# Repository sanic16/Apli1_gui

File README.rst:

============================
IOT Electrónica Aplicada 1
============================

Descripción
===========

Este es un repositorio que contiene el software de comunicación M.Q.T.T. para dispositivos
ESP8266 y ESP32, además de interfaces gráficas para su control.

Autores
========
Julio Sanic, 2022
Alejandro Camey, 2022

Requerimientos
===============

* Python3
* Tkinter
* Micropython

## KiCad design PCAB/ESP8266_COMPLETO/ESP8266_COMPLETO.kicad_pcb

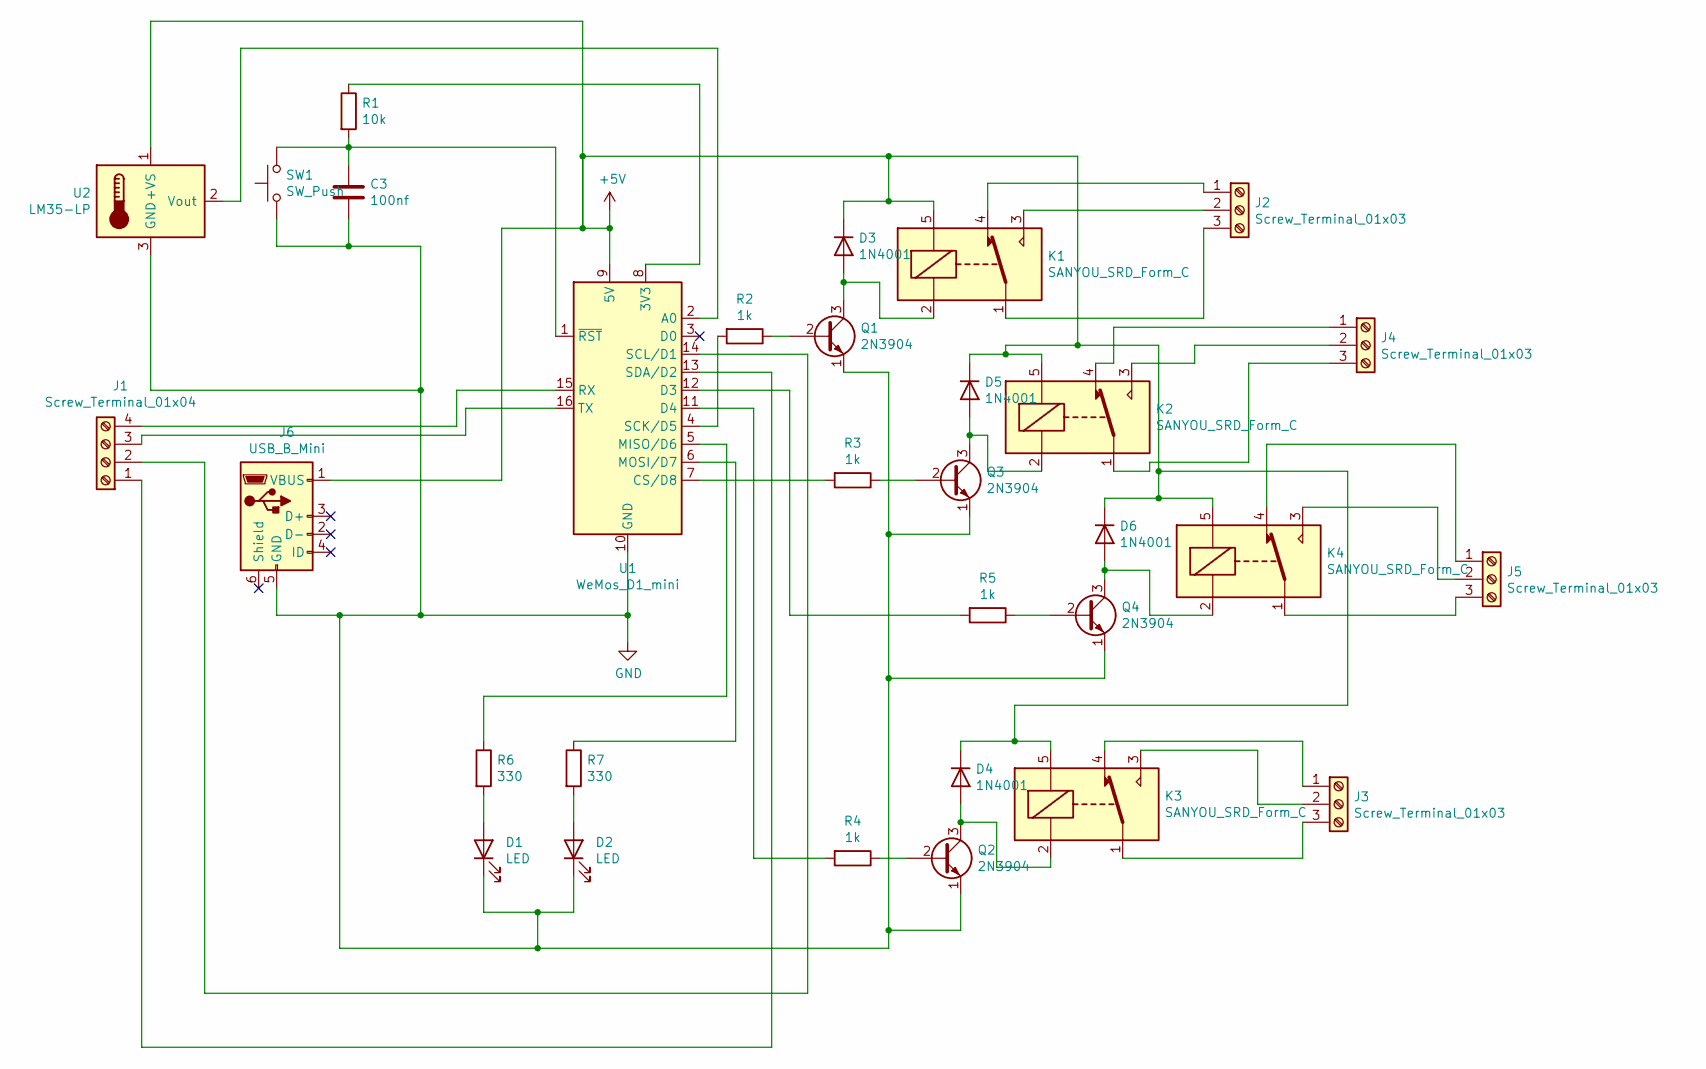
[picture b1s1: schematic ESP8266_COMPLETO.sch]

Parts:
C3: 100nf; C_Disc_D5.0mm_W2.5mm_P5.00mm
D1, D2: LED; LED_D5.0mm
D3, D4, D5, D6: 1N4001; D_DO-41_SOD81_P10.16mm_Horizontal
J1: Screw_Terminal_01x04; FanPinHeader_1x04_P2.54mm_Vertical
J2, J3, J4, J5: Screw_Terminal_01x03; TerminalBlock_Phoenix_MKDS-1,5-3-5.08_1x03_P5.08mm_Horizont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
J6: USB_B_Mini; USB_Mini-B_Lumberg_2486_01_Horizontal
K1, K2, K3, K4: SANYOU_SRD_Form_C; Relay_SPDT_SANYOU_SRD_Series_Form_C
Q1, Q2, Q3, Q4: 2N3904; TO-92_Inline
R1: 10k; R_Axial_DIN0204_L3.6mm_D1.6mm_P7.62mm_Horizontal
R2, R3, R4, R5: 1k; R_Axial_DIN0204_L3.6mm_D1.6mm_P7.62mm_Horizontal
R6, R7: 330; R_Axial_DIN0204_L3.6mm_D1.6mm_P7.62mm_Horizontal
SW1: SW_Push; SW_PUSH_6mm
U1: WeMos_D1_mini; WEMOS_D1_mini_light
U2: LM35-LP; TO-92_Inline

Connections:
+5V: D3.1 (K), D4.1 (K), D5.1 (K), D6.1 (K), J6.1 (VBUS), K1.5, K2.5, K3.5, K4.5, U1.9 (5V), U2.1 (+VS)
GND: C3.2, D1.1 (K), D2.1 (K), J6.5 (GND), Q1.1 (E), Q2.1 (E), Q3.1 (E), Q4.1 (E), SW1.1, U1.10 (GND), U2.3 (GND)
unnamed: C3.1, R1.2, SW1.2, U1.1 (~RST)
unnamed: D1.2 (A), R6.2
unnamed: D2.2 (A), R7.2
unnamed: D3.2 (A), K1.2, Q1.3 (C)
unnamed: D4.2 (A), K3.2, Q2.3 (C)
unnamed: D5.2 (A), K2.2, Q3.3 (C)
unnamed: D6.2 (A), K4.2, Q4.3 (C)
unnamed: J1.1, U1.13 (SDA/D2)
unnamed: J1.2, U1.14 (SCL/D1)
unnamed: J1.3, U1.16 (TX)
unnamed: J1.4, U1.15 (RX)
unnamed: J2.1, K1.4
unnamed: J2.2, K1.3
unnamed: J2.3, K1.1
unnamed: J3.1, K3.4
unnamed: J3.2, K3.3
unnamed: J3.3, K3.1
unnamed: J4.1, K2.4
unnamed: J4.2, K2.3
unnamed: J4.3, K2.1
unnamed: J5.1, K4.4
unnamed: J5.2, K4.3
unnamed: J5.3, K4.1
unnamed: Q1.2 (B), R2.1
unnamed: Q2.2 (B), R4.1
unnamed: Q3.2 (B), R3.1
unnamed: Q4.2 (B), R5.1
unnamed: R1.1, U1.8 (3V3)
unnamed: R2.2, U1.4 (SCK/D5)
unnamed: R3.2, U1.7 (CS/D8)
unnamed: R4.2, U1.11 (D4)
unnamed: R5.2, U1.12 (D3)
unnamed: R6.1, U1.5 (MISO/D6)
unnamed: R7.1, U1.6 (MOSI/D7)
unnamed: U1.2 (A0), U2.2 (Vout)

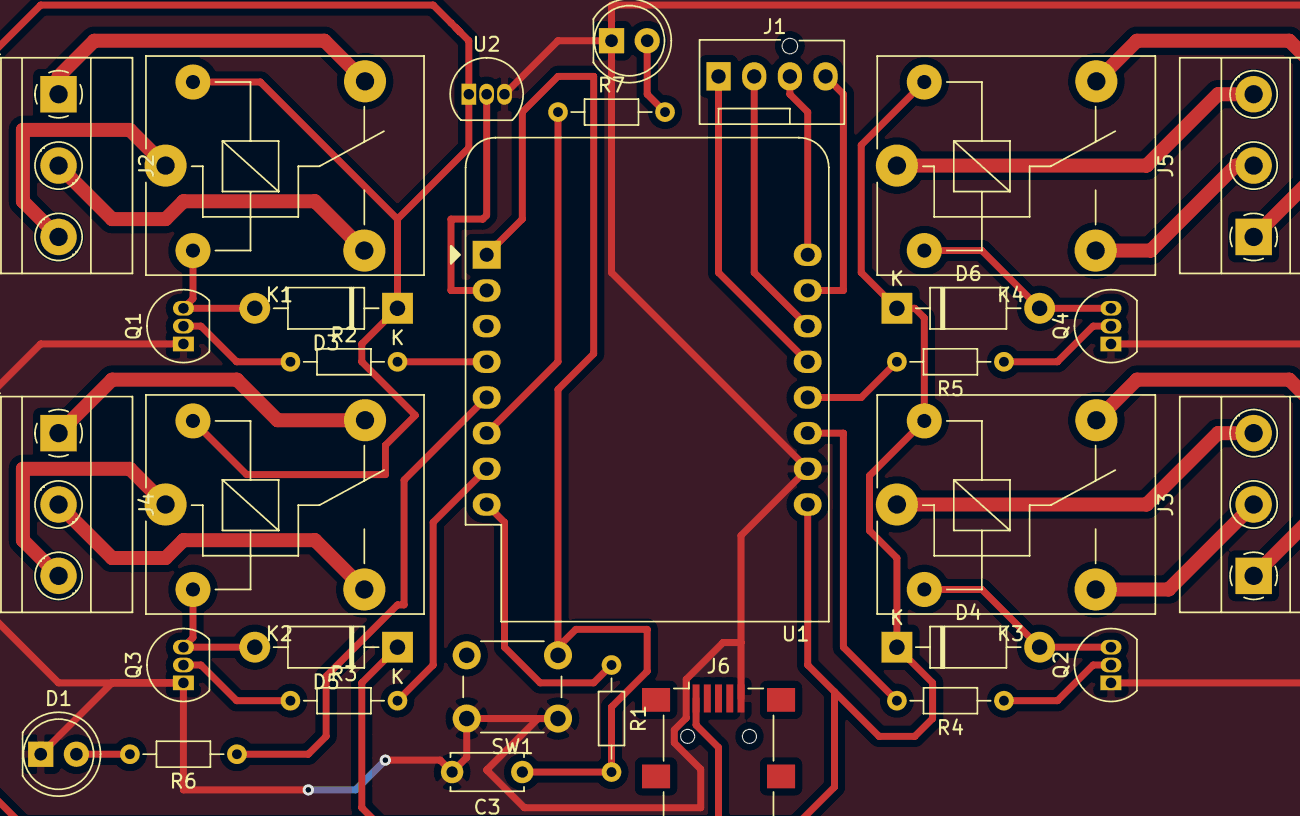
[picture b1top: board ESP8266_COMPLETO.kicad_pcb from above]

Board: 2 copper layers, 31 parts (0 on the bottom side), 37 nets.

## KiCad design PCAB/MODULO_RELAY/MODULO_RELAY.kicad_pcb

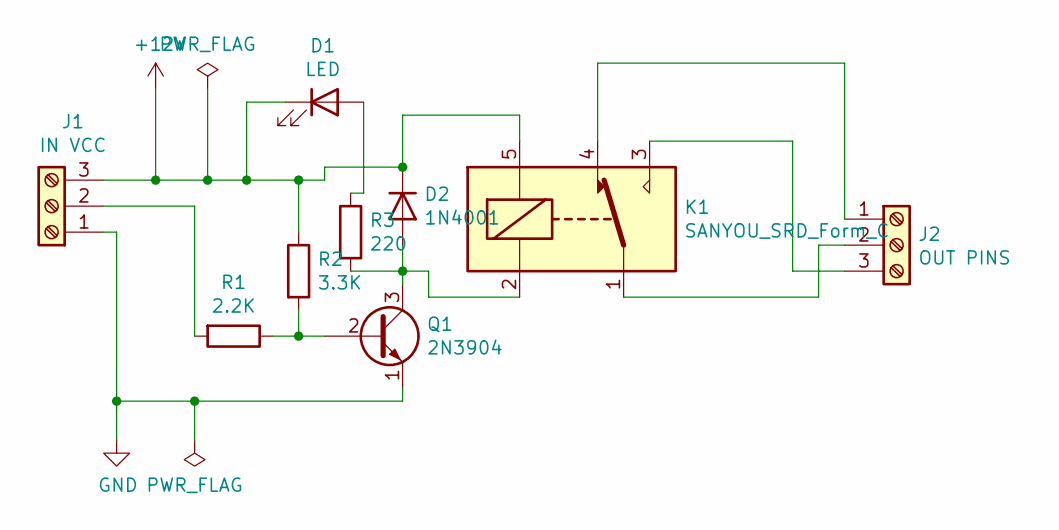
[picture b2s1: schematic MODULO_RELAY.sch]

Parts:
D1: LED; LED_D5.0mm
D2: 1N4001; D_DO-41_SOD81_P10.16mm_Horizontal
J1: IN VCC; FanPinHeader_1x03_P2.54mm_Vertical
J2: OUT PINS; FanPinHeader_1x03_P2.54mm_Vertical
K1: SANYOU_SRD_Form_C; Relay_SPDT_SANYOU_SRD_Series_Form_C
Q1: 2N3904; TO-92_Inline
R1: 2.2K; R_Axial_DIN0204_L3.6mm_D1.6mm_P2.54mm_Vertical
R2: 3.3K; R_Axial_DIN0204_L3.6mm_D1.6mm_P2.54mm_Vertical
R3: 220; R_Axial_DIN0204_L3.6mm_D1.6mm_P2.54mm_Vertical

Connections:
+12V: D1.1 (K), D2.1 (K), J1.3, K1.5, R2.1
GND: J1.1, Q1.1 (E)
unnamed: D1.2 (A), R3.1
unnamed: D2.2 (A), K1.2, Q1.3 (C), R3.2
unnamed: J1.2, R1.2
unnamed: J2.1, K1.4
unnamed: J2.2, K1.1
unnamed: J2.3, K1.3
unnamed: Q1.2 (B), R1.1, R2.2

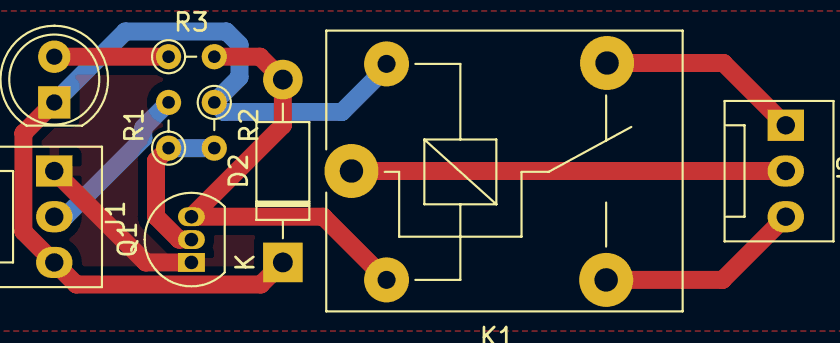
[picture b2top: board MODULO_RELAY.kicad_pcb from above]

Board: 2 copper layers, 9 parts (0 on the bottom side), 9 nets.

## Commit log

2022-10-06 Comenzando Proyecto
2022-10-08 Configurando GUI
2022-10-08 borrando venv
2022-10-16 Agregando PCB 1
2022-10-17 kicad
2022-10-24 PCB relays completa
2022-10-25 agregando bitacora 4
2022-10-25 Agregando bitacora 5
2022-10-26 Cambios
2022-10-30 Agregando PCB2
